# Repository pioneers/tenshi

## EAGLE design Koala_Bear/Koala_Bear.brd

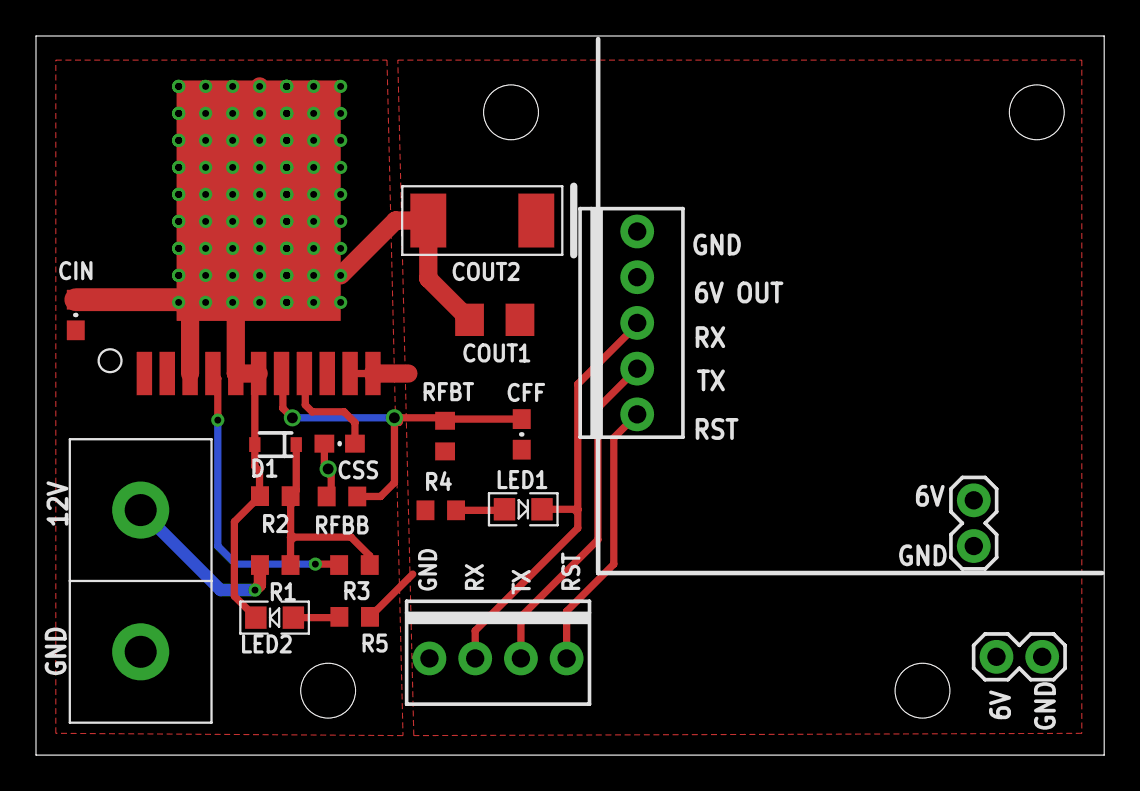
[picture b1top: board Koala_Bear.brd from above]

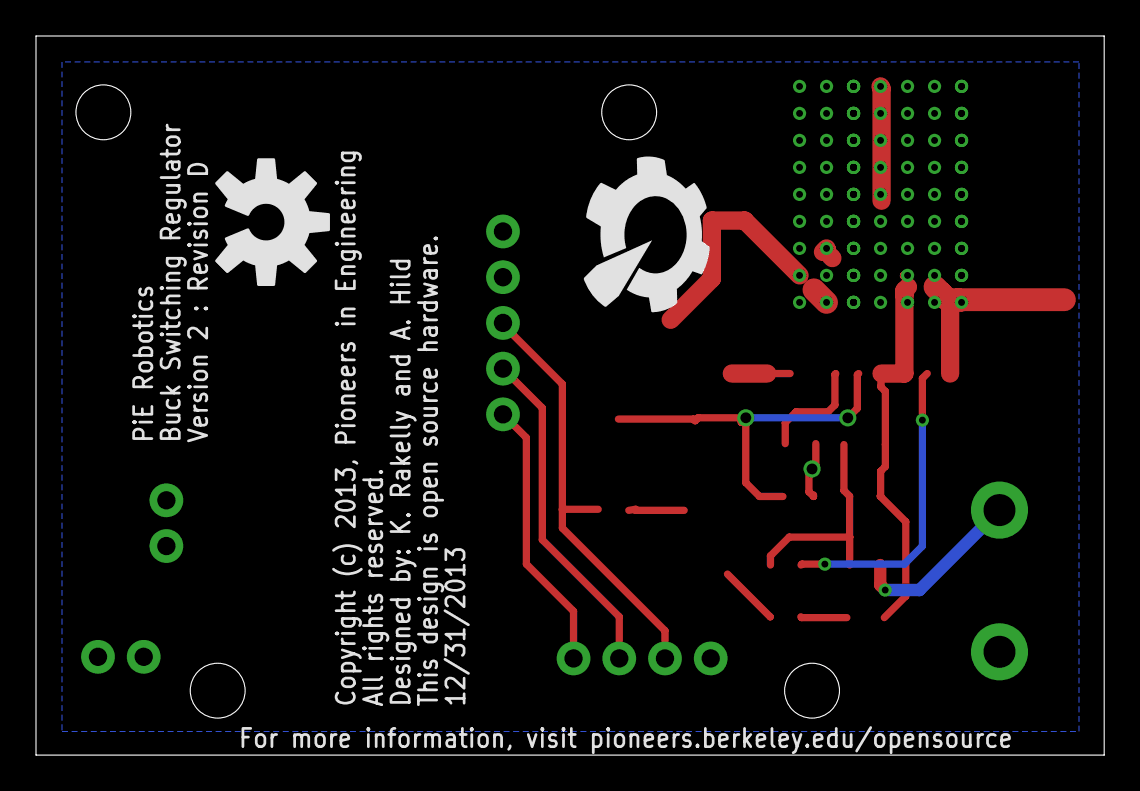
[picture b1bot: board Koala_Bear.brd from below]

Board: 2 copper layers, 59.3 x 40.0 mm, 27 parts (2 on the bottom side), 12 nets.

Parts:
CFF: 4.7nf; 0603-CAP
CIN: 10uF; 0603-CAP
COUT1: 47uF; 1206
COUT2: 470uF; TANT_CASE_E
CSS: .47uF; 0603-CAP
D1: 5.1V; SOD-323
LED1: GRN; LED-0805
LED2: YEL; LED-0805
MSTRO_PINS: 1X04-MTA
MSTRO_PWR: 1X05-MTA
PWR: ANDERSONVERTICAL; ANDERSON_VERTICAL
R1: 60k; R0603
R2: 30k; R0603
R3: 100; R0603
R4, R5: 330; R0603
RFBB: 2.37k; R0603
RFBT: 15.4k; R0603
SERVO_PWR_6, SERVO_PWR_12: 1X02
U$1: LMZ12010
U$2, U$3, U$4, U$5: STAND-OFF-TIGHT
U$10: PIE-LOGO-SMALL
U$11: OSHW-LOGO-L

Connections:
DIODE: D1.1, R1.1, R2.2, R3.1
EN: R3.2, U$1.4
FB: CFF.2, RFBB.1, RFBT.1, U$1.7
GND: CIN.2, COUT1.2, COUT2.NEG, CSS.2, D1.2, LED2.C, MSTRO_PINS.1, MSTRO_PWR.5, PWR.PIN1, R2.1, RFBB.2, SERVO_PWR_6.2, SERVO_PWR_12.1, U$1.3, U$1.5, U$1.6, U$1.GND
unnamed: LED1.A, R4.1
unnamed: LED2.A, R5.1
RST: MSTRO_PINS.4, MSTRO_PWR.1
RX: LED1.C, MSTRO_PINS.2, MSTRO_PWR.3
SS: CSS.1, U$1.8
TX: MSTRO_PINS.3, MSTRO_PWR.2
VIN: CIN.1, PWR.PIN2, R1.2, U$1.1, U$1.2
VOUT: CFF.1, COUT1.1, COUT2.POS, MSTRO_PWR.4, R4.2, R5.2, RFBT.2, SERVO_PWR_6.1, SERVO_PWR_12.2, U$1.10, U$1.11

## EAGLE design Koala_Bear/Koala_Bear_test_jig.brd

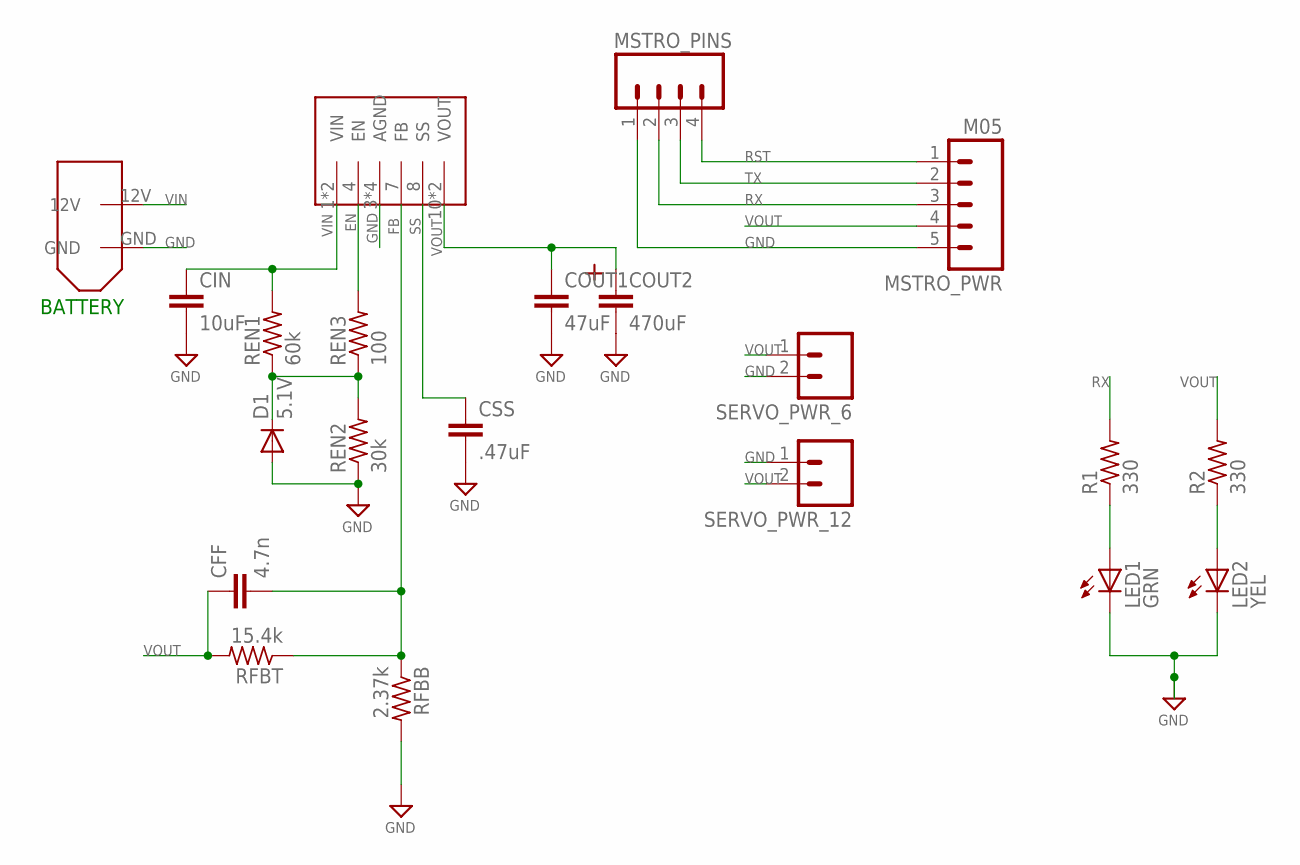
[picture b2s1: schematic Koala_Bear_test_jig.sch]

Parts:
CFF: 4.7n; 0603-CAP
CIN: 10uF; 0603-CAP
COUT1: 47uF; 1206
COUT2: 470uF; TANT_CASE_E
CSS: .47uF; 0603-CAP
D1: 5.1V; SOD-323
LED1: GRN; CHIP-LED0805
LED2: YEL; CHIP-LED0805
MSTRO_PINS: M041X04-MTA; 1X04-MTA
MSTRO_PWR: M05; 1X05-MTA
R1, R2: 330; R0603
REN1: 60k; R0603
REN2: 30k; R0603
REN3: 100; R0603
RFBB: 2.37k; R0603
RFBT: 15.4k; R0603
SERVO_PWR_6, SERVO_PWR_12: M02PTH; 1X02
U$1: LMZ12010
XT60: XT60CONNECTOR

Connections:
DIODE: D1.1 (C), REN1.1, REN2.2, REN3.1
EN: REN3.2, U$1.4 (EN)
FB: CFF.2, RFBB.1, RFBT.1, U$1.7 (FB)
GND: CIN.2, COUT1.2, COUT2.NEG, CSS.2, D1.2 (A), LED1.C, LED2.C, MSTRO_PINS.1, MSTRO_PWR.5, REN2.1, RFBB.2, SERVO_PWR_6.2, SERVO_PWR_12.1, U$1.3 (AGND), U$1.5 (AGND), U$1.6 (AGND), U$1.GND (AGND), XT60.GND
unnamed: LED1.A, R1.1
unnamed: LED2.A, R2.1
RST: MSTRO_PINS.4, MSTRO_PWR.1
RX: MSTRO_PINS.2, MSTRO_PWR.3, R1.2
SS: CSS.1, U$1.8 (SS)
TX: MSTRO_PINS.3, MSTRO_PWR.2
VIN: CIN.1, REN1.2, U$1.1 (VIN), U$1.2 (VIN), XT60.12V
VOUT: CFF.1, COUT1.1, COUT2.POS, MSTRO_PWR.4, R2.2, RFBT.2, SERVO_PWR_6.1, SERVO_PWR_12.2, U$1.10 (VOUT), U$1.11 (VOUT)

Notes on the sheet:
BATTERY

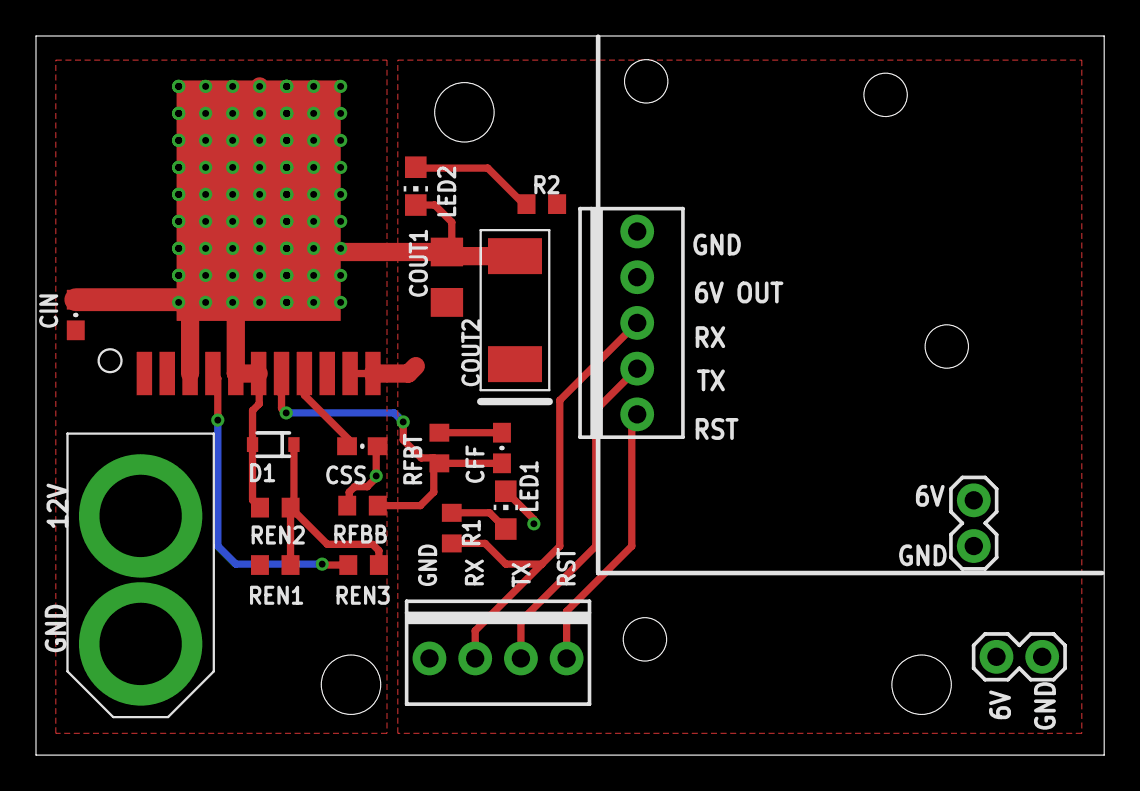
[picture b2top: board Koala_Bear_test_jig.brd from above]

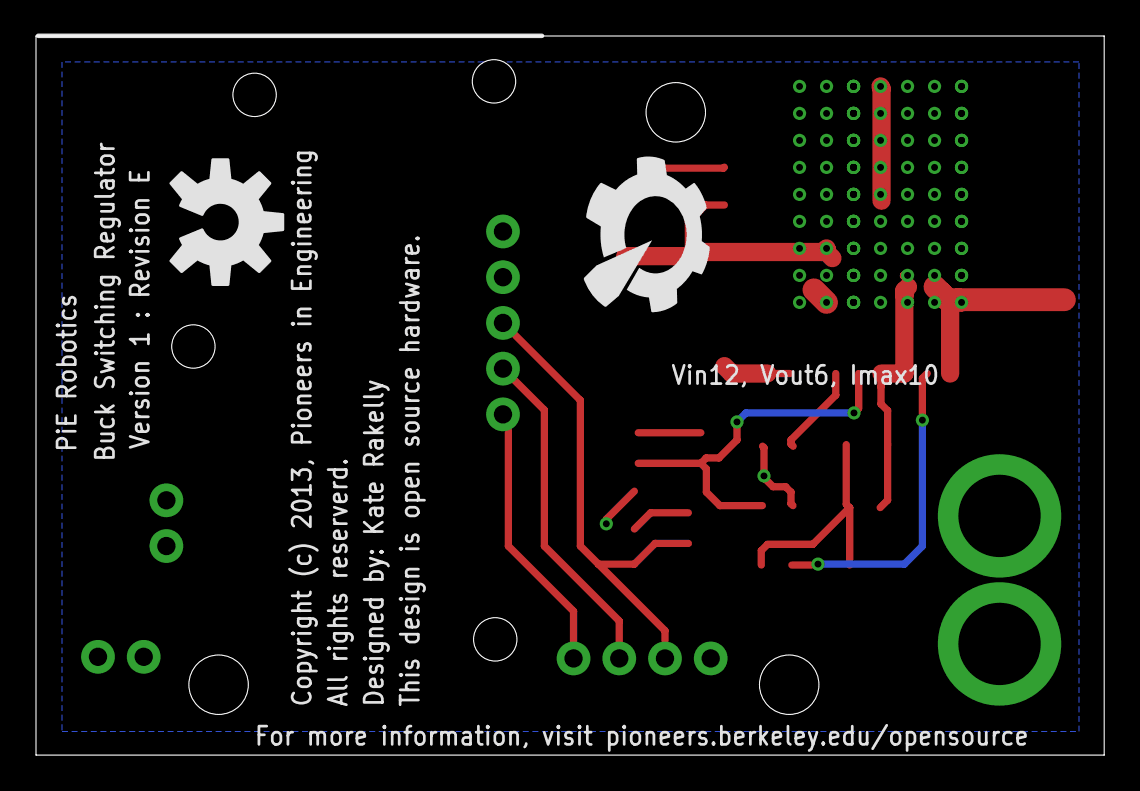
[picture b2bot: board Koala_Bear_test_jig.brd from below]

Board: 2 copper layers, 59.3 x 40.0 mm, 30 parts (2 on the bottom side), 12 nets.

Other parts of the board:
U$2, U$6, U$7, U$8: STAND_OFF_SERVOC
U$3, U$4, U$5: STAND-OFF
U$10: PIE-LOGO-SMALL
U$11: OSHW-LOGO-L

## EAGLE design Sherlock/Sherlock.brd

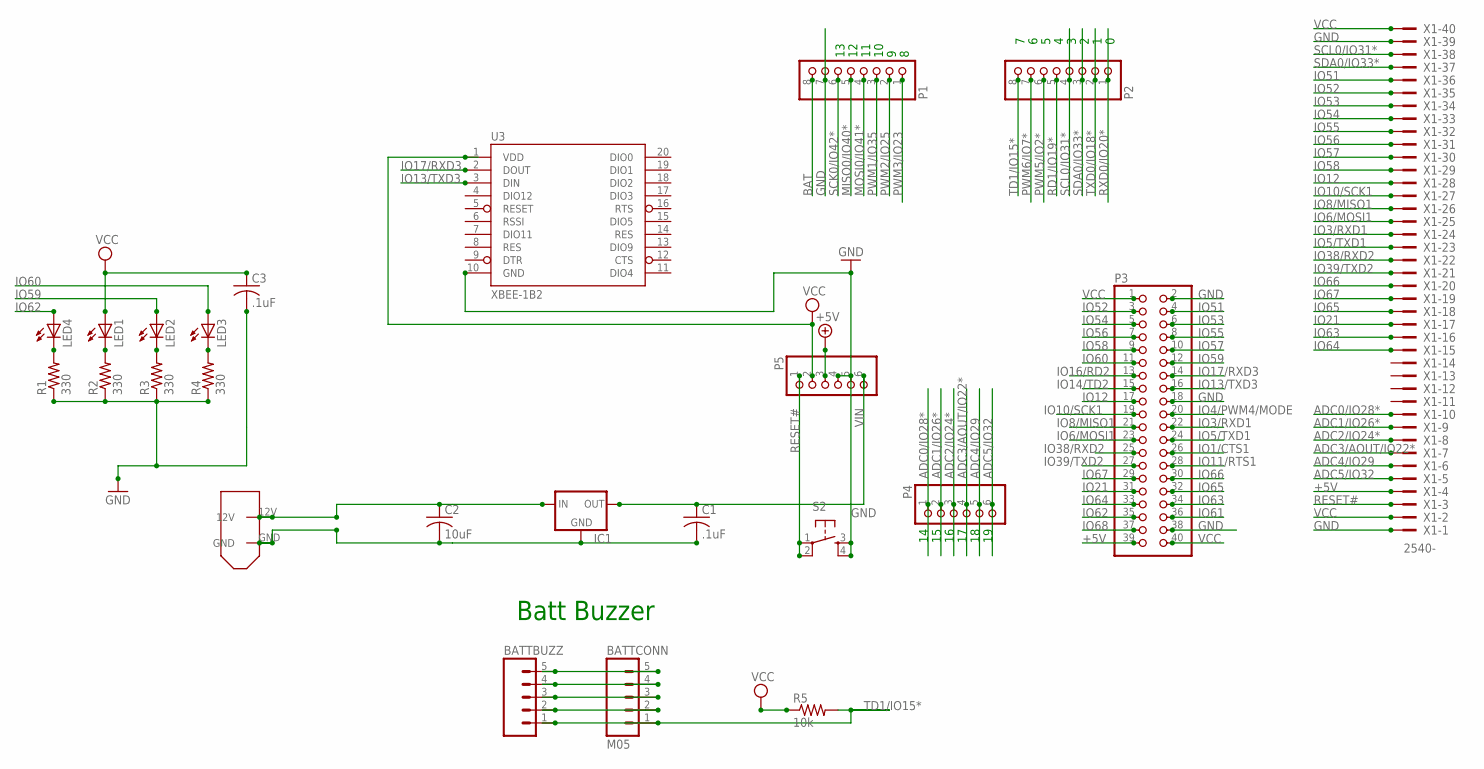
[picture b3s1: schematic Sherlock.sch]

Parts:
BATTBUZZ: M05PTH; 1X05
BATTCONN: M05; 1X05
C1: .1uF; C0603
C2: 10uF; C0603
C3: .1uF; C0603K
IC1: 78XXL
LED1, LED2, LED3, LED4: LED0603; LED-0603
P1, P2: PINHD-1X08_2.54-S; 1X08-S
P3: PINHD-2X20; 2X20
P4, P5: PINHD-1X06_2.54-S; 1X06-S
R1, R2, R3, R4: 330; R0603
R5: 10k; R0603
S2: TAC_SWITCHPTH; TACTILE-PTH
U3: XBEE-1B2; XBEE-SILK
U$1: XT60CONNECTOR
X1: 2540-; PAK100/2500-40

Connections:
12V: C2.1, IC1.IN, U$1.12V
+5V: P3.39, P5.3, X1.4
ADC0/IO28*: P4.1, X1.10
ADC1/IO26*: P4.2, X1.9
ADC2/IO24*: P4.3, X1.8
ADC3/AOUT/IO22*: P4.4, X1.7
ADC4/IO29: P4.5, X1.6
ADC5/IO32: P4.6, X1.5
BAT: P1.8
GND: C1.2, C2.2, C3.2, IC1.GND, P1.7, P3.2, P3.18, P3.38, P5.4, P5.5, R1.1, R2.1, R3.1, R4.1, S2.3, S2.4, U3.10 (GND), U$1.GND, X1.1, X1.39
IO1/CTS1: P3.26
IO3/RXD1: P3.22, X1.24
IO4/PWM4/MODE: P3.20
IO5/TXD1: P3.24, X1.23
IO6/MOSI1: P3.23, X1.25
IO8/MISO1: P3.21, X1.26
IO10/SCK1: P3.19, X1.27
IO11/RTS1: P3.28
IO12: P3.17, X1.28
IO13/TXD3: P3.16, U3.3 (DIN)
IO14/TD2: P3.15
IO16/RD2: P3.13
IO17/RXD3: P3.14, U3.2 (DOUT)
IO21: P3.31, X1.17
IO38/RXD2: P3.25, X1.22
IO39/TXD2: P3.27, X1.21
IO51: P3.4, X1.36
IO52: P3.3, X1.35
IO53: P3.6, X1.34
IO54: P3.5, X1.33
IO55: P3.8, X1.32
IO56: P3.7, X1.31
IO57: P3.10, X1.30
IO58: P3.9, X1.29
IO59: LED2.A, P3.12
IO60: LED3.A, P3.11
IO61: P3.36
IO62: LED4.A, P3.35
IO63: P3.34, X1.16
IO64: P3.33, X1.15
IO65: P3.32, X1.18
IO66: P3.30, X1.20
IO67: P3.29, X1.19
IO68: P3.37
MISO0/IO40*: P1.5
MOSI0/IO41*: P1.4
unnamed: LED4.C, R1.2
unnamed: LED1.C, R2.2
unnamed: LED2.C, R3.2
unnamed: BATTBUZZ.5, BATTCONN.5
unnamed: BATTBUZZ.4, BATTCONN.4
unnamed: BATTBUZZ.3, BATTCONN.3
unnamed: BATTBUZZ.2, BATTCONN.2
unnamed: LED3.C, R4.2
PWM1/IO35: P1.3
PWM2/IO25: P1.2
PWM3/IO23: P1.1
PWM5/IO2*: P2.6
PWM6/IO7*: P2.7
RD1/IO19*: P2.5
RESET#: P5.1, S2.1, S2.2, X1.3
RXD0/IO20*: P2.1
SCK0/IO42*: P1.6
SCL0/IO31*: P2.4, X1.38
SDA0/IO33*: P2.3, X1.37
TD1/IO15*: BATTBUZZ.1, BATTCONN.1, P2.8, R5.2
TXD0/IO18*: P2.2
VCC: C3.1, LED1.A, P3.1, P3.40, P5.2, R5.1, U3.1 (VDD), X1.2, X1.40
VIN: C1.1, IC1.OUT, P5.6

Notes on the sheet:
Batt Buzzer

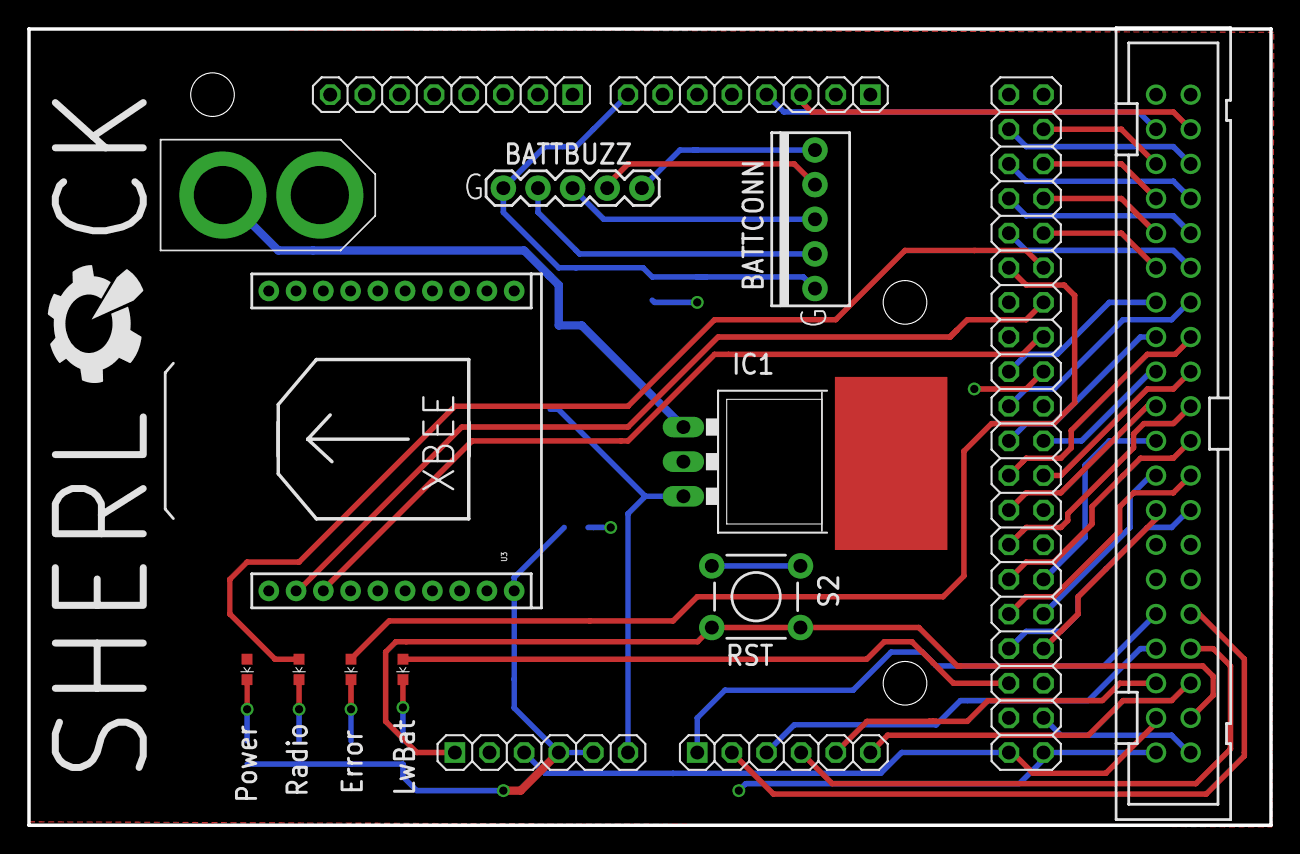
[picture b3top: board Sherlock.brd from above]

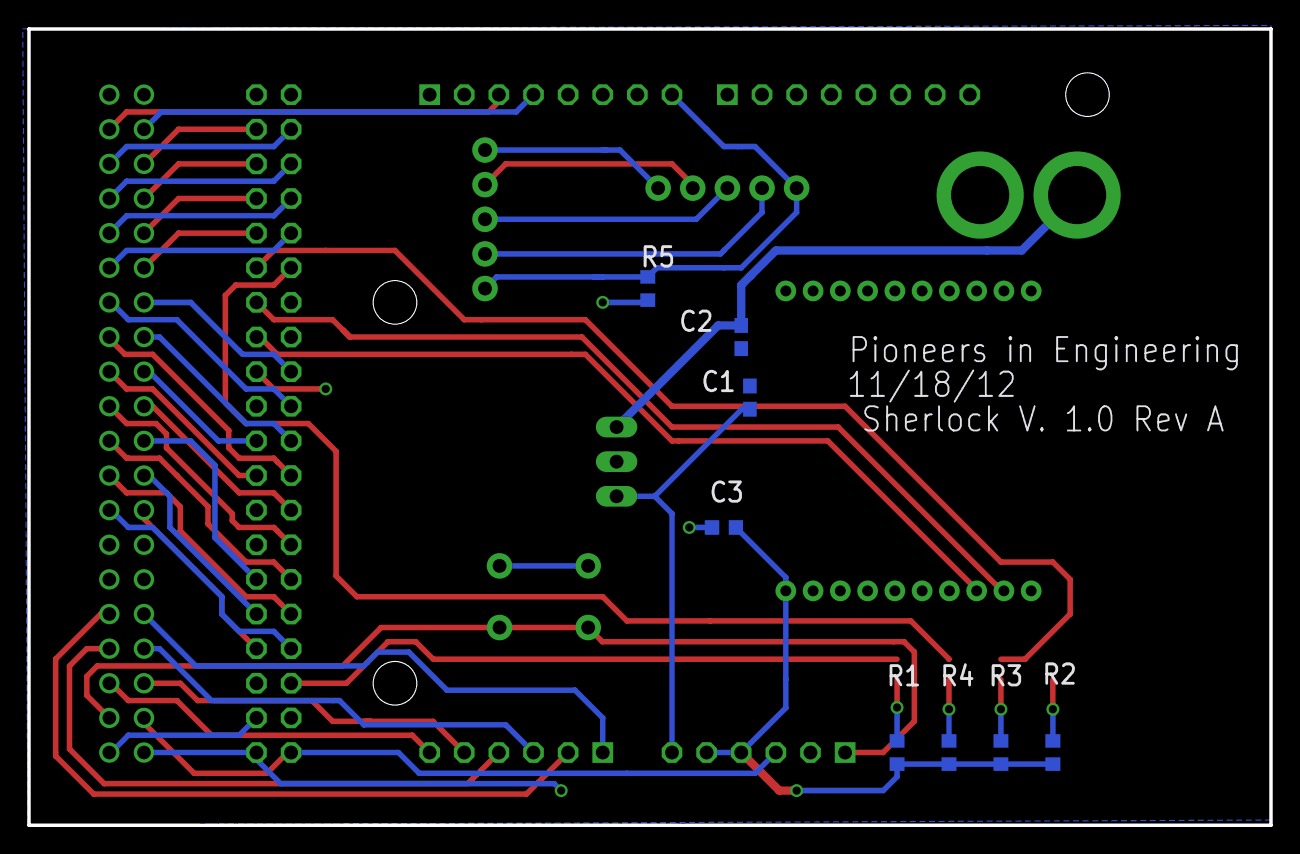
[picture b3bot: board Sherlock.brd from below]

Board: 2 copper layers, 91.1 x 58.4 mm, 25 parts (8 on the bottom side), 50 nets.

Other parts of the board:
U$2: SHERLOCK

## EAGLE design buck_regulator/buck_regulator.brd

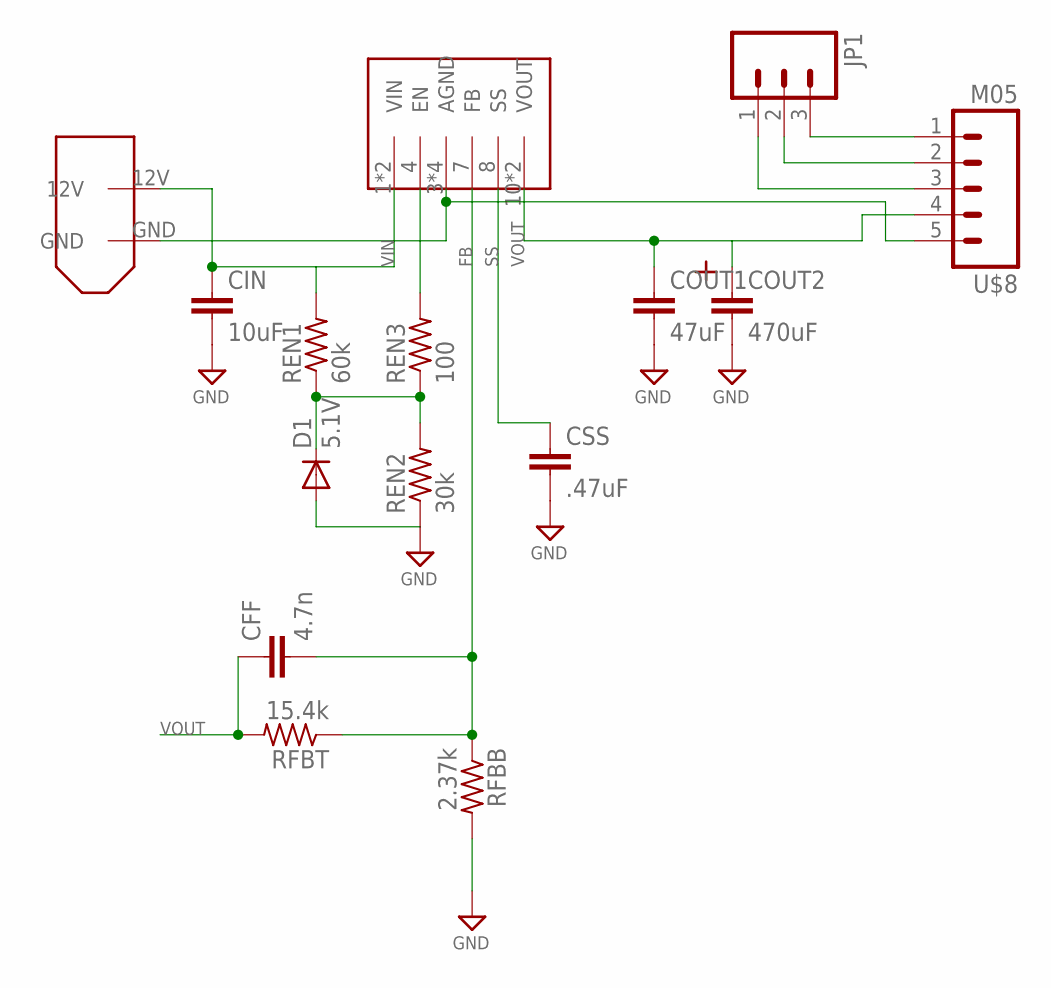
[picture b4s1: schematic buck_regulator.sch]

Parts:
CFF: 4.7n; 0603-CAP
CIN: 10uF; 0603-CAP
COUT1: 47uF; 1206
COUT2: 470uF; TANT_CASE_E
CSS: .47uF; 0603-CAP
D1: 5.1V; SOD-323
JP1: M03MTA1X3; 1X03
REN1: 60k; R0603
REN2: 30k; R0603
REN3: 100; R0603
RFBB: 2.37k; R0603
RFBT: 15.4k; R0603
U$1: LMZ12010
U$2: XT60CONNECTOR
U$8: M05; 1X05-MTA

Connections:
FB: CFF.2, RFBB.1, RFBT.1, U$1.7 (FB)
GND: CIN.2, COUT1.2, COUT2.NEG, CSS.2, D1.2 (A), REN2.1, RFBB.2, U$1.3 (AGND), U$1.5 (AGND), U$1.6 (AGND), U$1.GND (AGND), U$2.GND, U$8.5
unnamed: REN3.2, U$1.4 (EN)
unnamed: JP1.1, U$8.3
unnamed: D1.1 (C), REN1.1, REN2.2, REN3.1
unnamed: JP1.2, U$8.2
unnamed: JP1.3, U$8.1
SS: CSS.1, U$1.8 (SS)
VIN: CIN.1, REN1.2, U$1.1 (VIN), U$1.2 (VIN), U$2.12V
VOUT: CFF.1, COUT1.1, COUT2.POS, RFBT.2, U$1.10 (VOUT), U$1.11 (VOUT), U$8.4

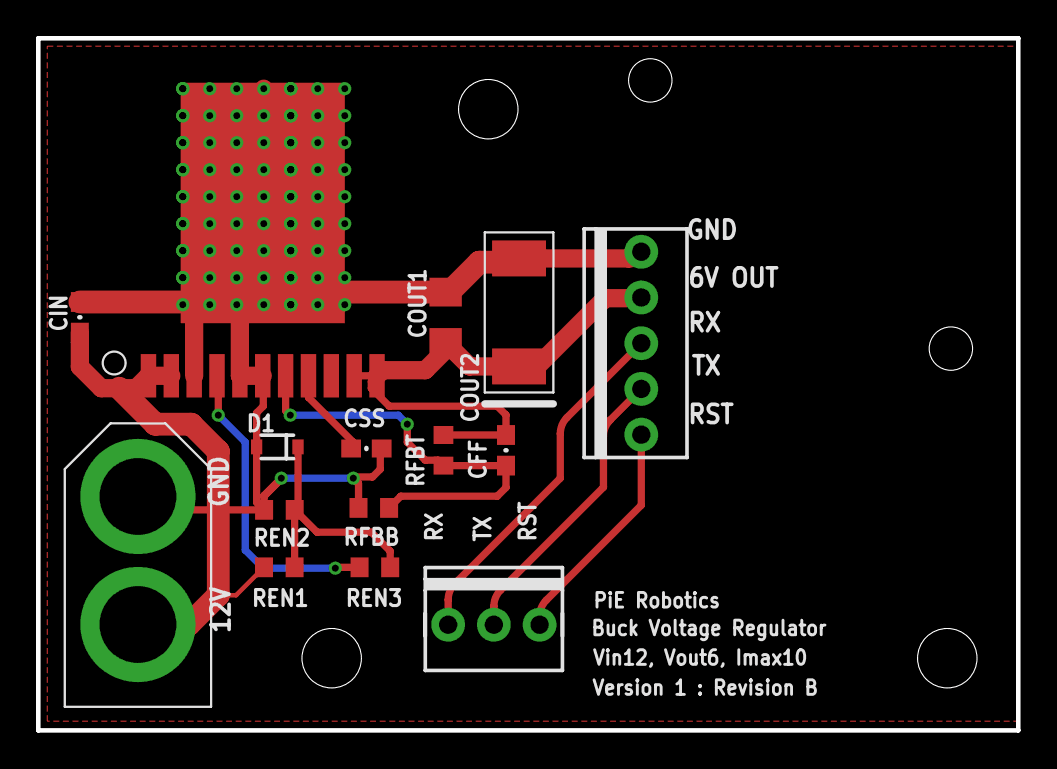
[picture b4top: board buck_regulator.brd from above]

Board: 2 copper layers, 54.4 x 38.5 mm, 20 parts (0 on the bottom side), 10 nets.

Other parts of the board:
U$3, U$4, U$5: STAND-OFF
U$6, U$7: STAND_OFF_SERVOC

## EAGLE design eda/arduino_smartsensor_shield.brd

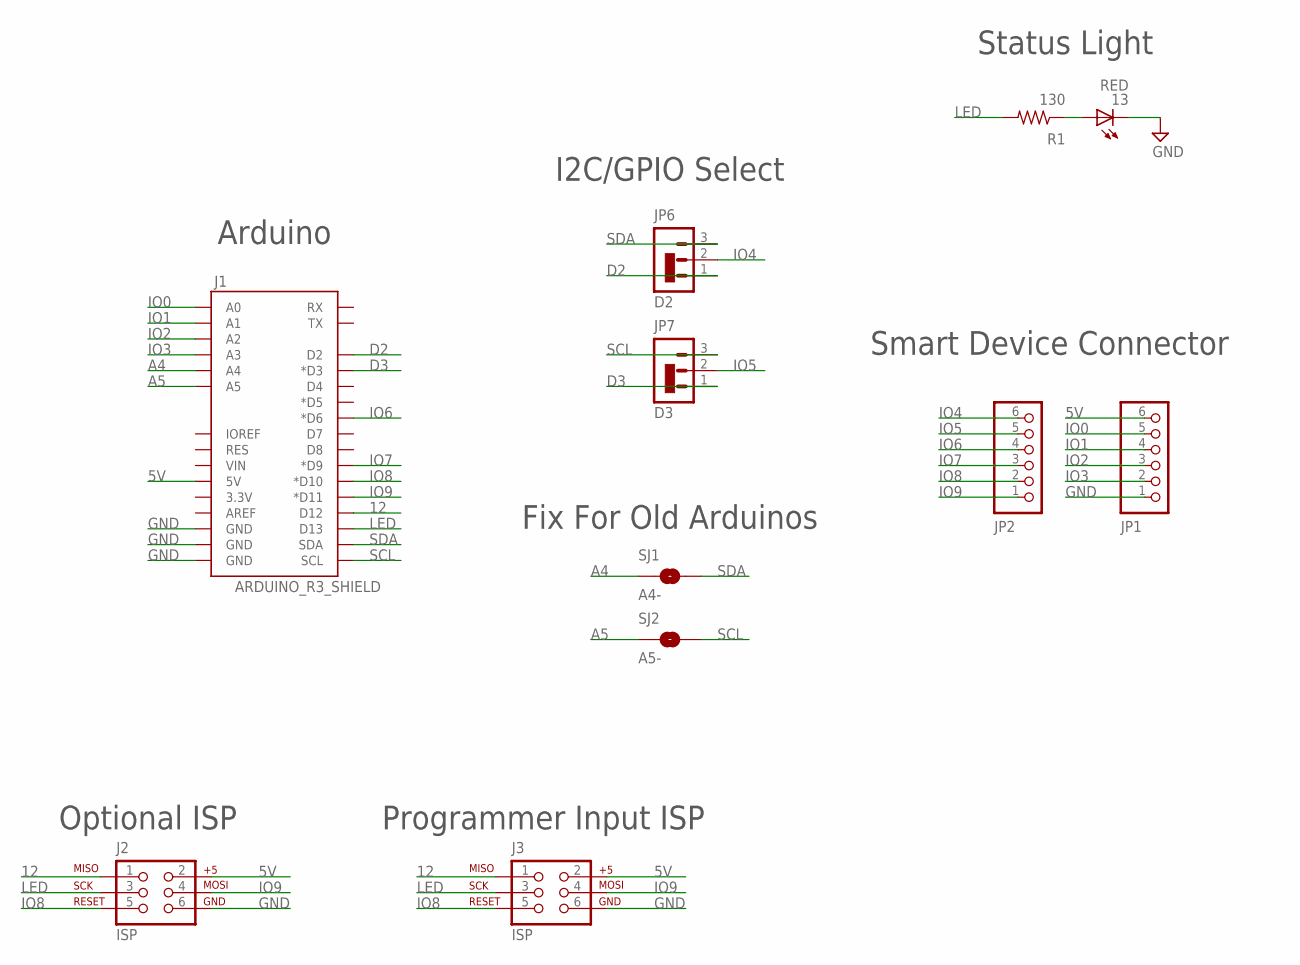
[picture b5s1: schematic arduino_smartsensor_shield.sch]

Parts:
13: RED; LED-0805
J1: ARDUINO_R3_SHIELD; UNO_R3_SHIELD
J2, J3: ISP; 2X3
JP1: PINHD-1X6STRAIN-RELIEF; 1X06-STRAINRELIEF
JP2: PINHD-1X6; 1X06
JP6: D2; 1X03-JMP-OPTION
JP7: D3; 1X03-JMP-OPTION
R1: 130; R0603
SJ1: A4-; SJ_2S-NO
SJ2: A5-; SJ_2S-NO

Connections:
5V: J1.5V, J2.2, J3.2, JP1.6
12: J1.D12, J2.1, J3.1
A4: J1.A4, SJ1.1
A5: J1.A5, SJ2.1
D2: J1.D2, JP6.1
D3: J1.D3 (*D3), JP7.1
GND: 13.C, J1.GND@0 (GND), J1.GND@1 (GND), J1.GND@2 (GND), J2.6, J3.6, JP1.1
IO0: J1.A0, JP1.5
IO1: J1.A1, JP1.4
IO2: J1.A2, JP1.3
IO3: J1.A3, JP1.2
IO4: JP2.6, JP6.2 (COMMON)
IO5: JP2.5, JP7.2 (COMMON)
IO6: J1.D6 (*D6), JP2.4
IO7: J1.D9 (*D9), JP2.3
IO8: J1.D10 (*D10), J2.5, J3.5, JP2.2
IO9: J1.D11 (*D11), J2.4, J3.4, JP2.1
LED: J1.D13, J2.3, J3.3, R1.2
unnamed: 13.A, R1.1
SCL: J1.SCL, JP7.3, SJ2.2
SDA: J1.SDA, JP6.3, SJ1.2

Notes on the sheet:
Arduino
I2C/GPIO Select
Fix For Old Arduinos
Smart Device Connector
Status Light
Optional ISP
Programmer Input ISP

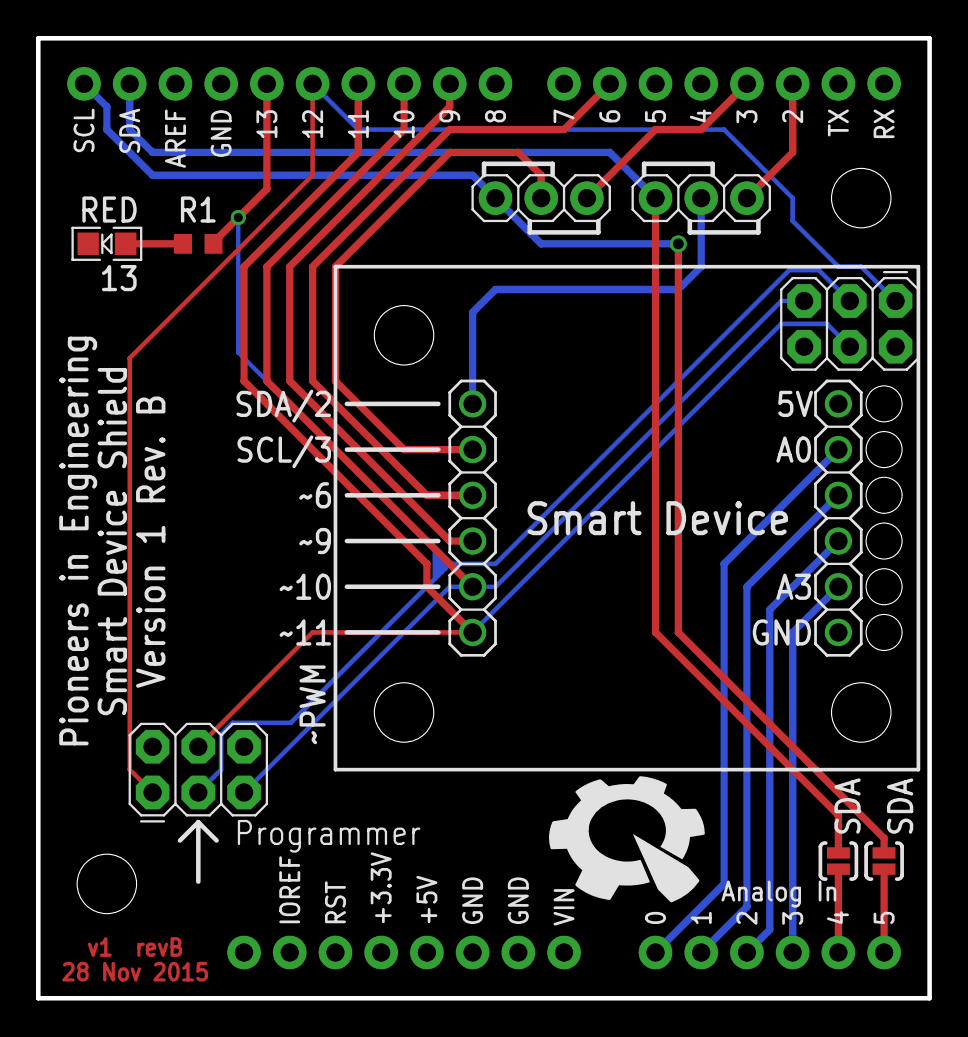
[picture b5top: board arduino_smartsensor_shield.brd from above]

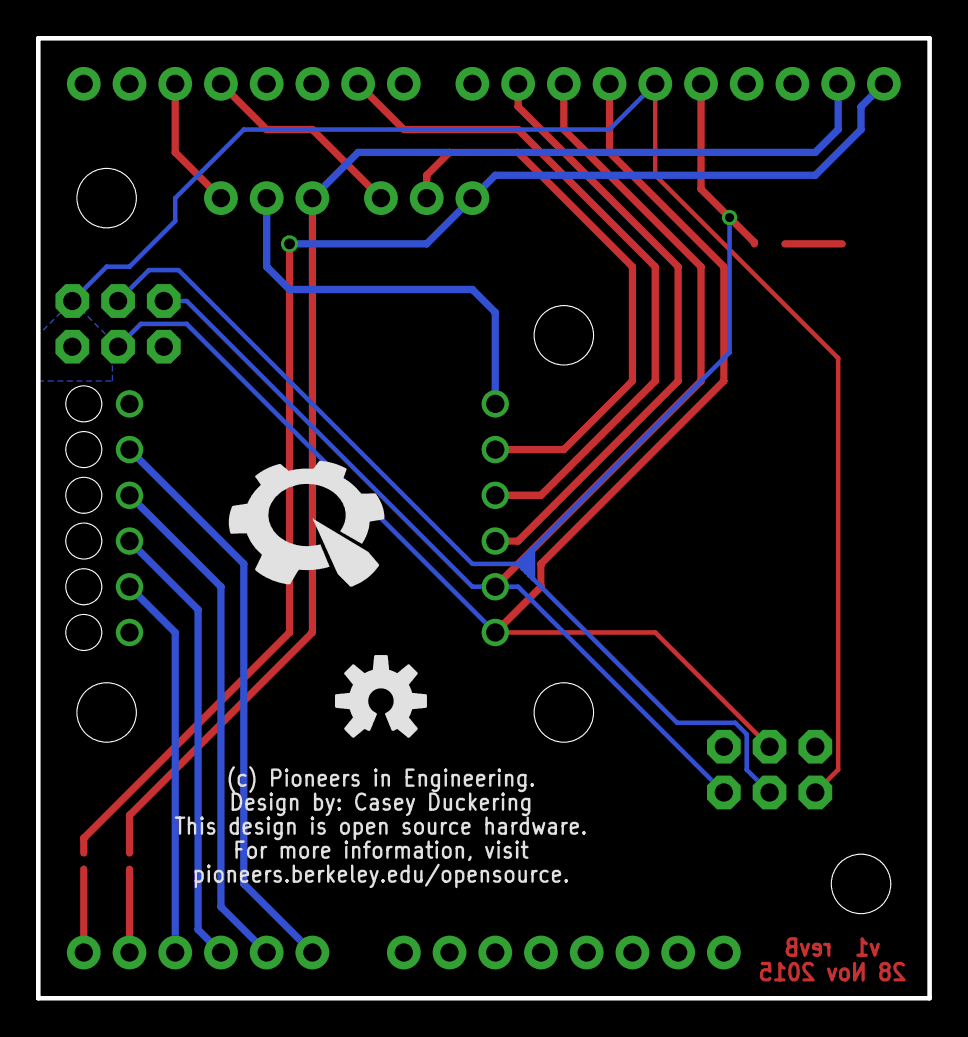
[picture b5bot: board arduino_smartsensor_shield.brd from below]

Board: 2 copper layers, 49.5 x 53.3 mm, 19 parts (2 on the bottom side), 21 nets.

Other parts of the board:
HOLE1, HOLE2, HOLE3, HOLE4, HOLE5: STAND-OFF
U$1, U$2: PIE-LOGO-SMALL
U$3: OSHW-LOGO-M

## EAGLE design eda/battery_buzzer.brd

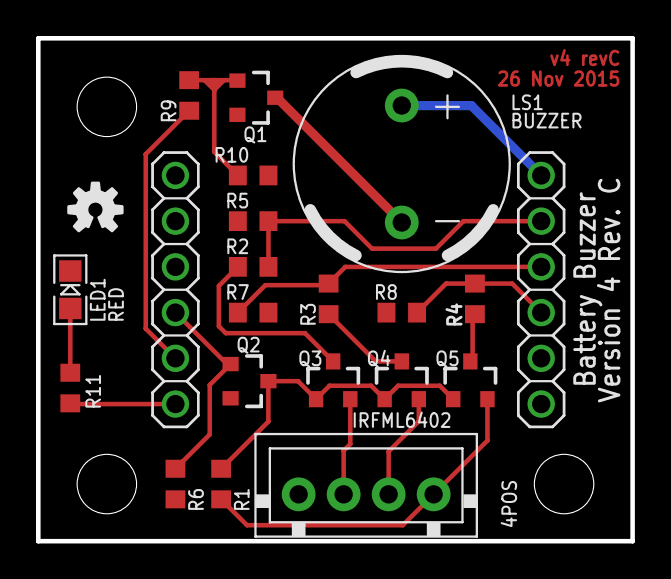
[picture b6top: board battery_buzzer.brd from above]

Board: 2 copper layers, 33.0 x 27.9 mm, 26 parts (1 on the bottom side), 18 nets.

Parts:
JP1, JP2: 1X06
LED1: RED; LED-0805
LS1: BUZZER; BUZZER_MAGNETIC_5V_12MM_RADIAL
Q1, Q2: IRFML8244; SOT23-3
Q3, Q4, Q5: P-CHANNEL-MOSFETSOT23-3; SOT23-3
R1, R2, R5, R6, R7, R8, R10: 10k; R0603
R3: 30k; R0603
R4: 51k; R0603
R9: 100; R0603
R11: 130; R0603
U$1: PIE-LOGO-SMALL
U$2, U$4, U$17: STAND-OFF
U$7: OSHW-LOGO-S
U$11: XH_CONN; XH_CONNECTOR_4POS_2.5MM

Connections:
5V: JP2.1, LS1.A
BCELL1: Q3.2, U$11.2
BCELL2: Q4.2, U$11.3
BCELL3: Q5.2, R1.2, U$11.4
BUZZER_SIGNAL: JP1.5, R9.1
DIV_EN: JP1.4, Q2.1, R6.2
GND: JP2.6, LED1.C, Q1.2, Q2.2, R5.1, R6.1, R7.1, R8.1, R10.1, U$11.1
IO0: JP2.2, R2.1, R5.2
IO1: JP2.3, R3.1, R7.2
IO2: JP2.4, R4.1, R8.2
LED_BUZZER: JP1.6, R11.2
unnamed: Q2.3, Q3.1, Q4.1, Q5.1, R1.1
unnamed: Q3.3, R2.2
unnamed: Q4.3, R3.2
unnamed: Q5.3, R4.2
unnamed: LS1.C, Q1.3
unnamed: Q1.1, R9.2, R10.2
unnamed: LED1.A, R11.1

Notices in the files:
Koala_Bear/Koala_Bear.brd:
Copyright (c) 2013, Pioneers in Engineering
All rights reserved.
parts and their libraries:
SparkFun: Licensing: CC v3.0 Share-Alike You are welcome to use this library for commercial purposes.
SparkFun-Boards: Licensing: Creative Commons ShareAlike 4.0 International - https://creativecommons.org/licenses/by-sa/4.0
